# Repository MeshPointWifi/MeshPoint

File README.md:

# MeshPoint
MeshPoint is Open source Wifi Hotspot for Crisis Situations
www.meshpointone.com

## MeshPoint v4.1

## Technical Specifications

- **CPU / SoC:** 700 MHz Quad-core Cortex-A7 / Qualcomm IPQ4018
- **RAM memory and storage:** 128 MB NAND and 8 MB NOR flash, 256 MB DDR3 RAM
- **Wi-Fi standards:** 802.11 a/b/g/n/ac Wave 2
- **Mesh protocol:** 802.11s mesh networking protocol
- **Radio:** 2.4 GHz and 5 GHz dual band
- **MIMO:** 2.4 GHz 2x2 MIMO / 5.8 GHz 2x2 MIMO
- **VLAN:** 802.1Q VLAN
- **Monitoring:** SNMP v2 / SNMP v3
- **Environment:** Indoor / Outdoor
- **Concurrent clients:** 300+
- **PoE mode:** Passive PoE in and PoE out
- **Power supply:** Battery powered, solar powered or PoE in
- **Antennas:** Internal dual-band antennas, 7 dBi
- **Wireless security:** WEP, WPA-PSK, WPA-Enterprise (WPA/WPA2, TKIP/AES), WPA3
- **Power consumption:** Average 4 W, maximum 12 W
- **Maximum TX power:** 20 dBm
- **Operating temperature:** -40 °C to 70 °C (-40 °F to 158 °F)
- **Licence:** Free
- **Available interfaces:** USB 2.0, USB 3.0, I2C, I2S, TDM, SPI, UART, GPIO, JTAG
- **Network ports:** 2x 1000BASE-T Ethernet ports
- **LTE modem option:** USB LTE Cat 4 modem

## New features

- [x] PoE Passtrough ( IN + OUT - daisy-chain )
- [x] On board sensor PRESSURE HUMIDITY TEMP
- [x] PCF8563T - on board RTC

## Licence

This project (hardware designs, 3D files and documentation) is released under the
**CERN Open Hardware Licence Version 2 - Strongly Reciprocal (CERN-OHL-S v2)**.

See the [LICENCE](LICENCE) file for the full text.
More info: https://cern-ohl.web.cern.ch/

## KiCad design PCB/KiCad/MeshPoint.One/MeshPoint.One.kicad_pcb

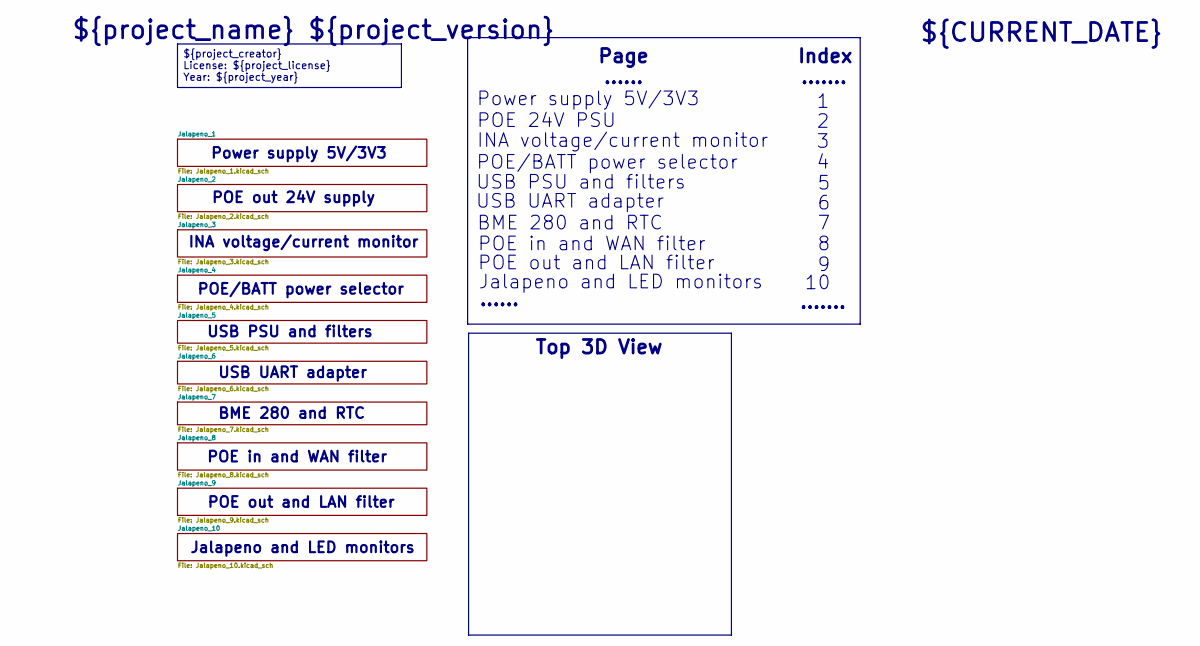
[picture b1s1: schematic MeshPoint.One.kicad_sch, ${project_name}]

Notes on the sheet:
POE/BATT power selector
${project_name} ${project_version}
Power supply 5V/3V3
Index
POE in and WAN filter
USB UART adapter
POE 24V PSU
POE out 24V supply
POE out and LAN filter
Jalapeno and LED monitors
BME 280 and RTC
INA voltage/current monitor
.......
USB PSU and filters
......
Page
Top 3D View
${CURRENT_DATE}
${project_creator} License: ${project_license} Year: ${project_year}

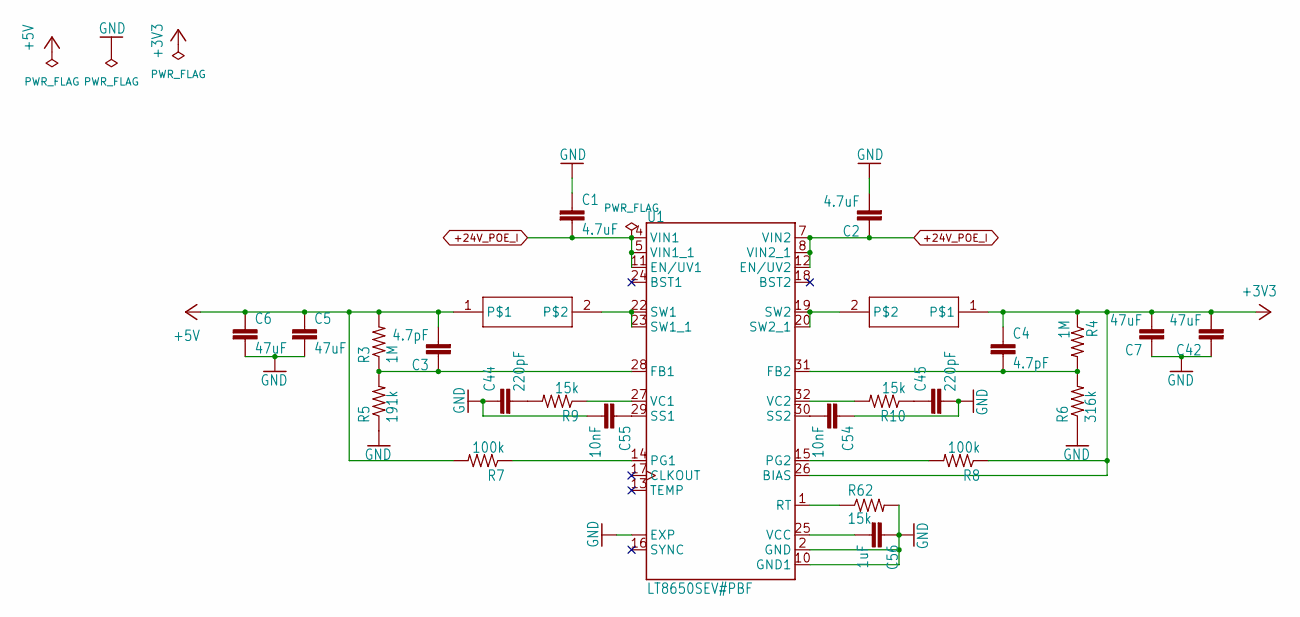
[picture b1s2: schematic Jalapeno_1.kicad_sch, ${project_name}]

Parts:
C1, C2: 4.7uF; C_1206_3216Metric; LCSC C29823
C3, C4: 4.7pF; C_0402_1005Metric; LCSC C1569
C5, C6, C7, C42: 47uF; C_1206_3216Metric; LCSC C96123
C44, C45: 220pF; C_0402_1005Metric; LCSC C1530
C54, C55: 10nF; C_0402_1005Metric; LCSC C1524
C56: 1uF; C_0402_1005Metric; LCSC C307413
L1, L2: PA4333.102NLTPA4333.102NLT; INDC6932X320; LCSC C5151941
R3, R4: 1M; R_0402_1005Metric; LCSC C279988
R5: 191k; R_0402_1005Metric; LCSC C852583
R6: 316k; R_0402_1005Metric; LCSC C25777
R7, R8: 100k; R_0402_1005Metric; LCSC C25741
R9, R10, R62: 15k; R_0402_1005Metric; LCSC C25756
U1: LT8650SEV#PBF; QFN50P600X400X103-32N240X440; Mouser 584-LT8650SEV#PBF

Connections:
+3V3: C4.1, C7.2, C42.2, L2.1, R4.1, R8.1, U1.26 (BIAS); also elsewhere on the board
+5V: C3.2, C5.1, C6.1, L1.1, R3.2, R7.2; also elsewhere on the board
+24V_POE_I: C1.2, C2.1, U1.4 (VIN1), U1.5 (VIN1_1), U1.7 (VIN2), U1.8 (VIN2_1), U1.11 (EN/UV1), U1.12 (EN/UV2); also elsewhere on the board
GND: C1.1, C2.2, C5.2, C6.2, C7.1, C42.1, C44.1, C45.2, C54.1, C55.2, C56.1, R5.1, R6.1, R62.2, U1.2 (GND), U1.10 (GND1), U1.33 (EXP), U1.34 (EXP), U1.35 (EXP), U1.36 (EXP), U1.37 (EXP), U1.38 (EXP); also elsewhere on the board
unnamed: C44.2, R9.2
unnamed: C45.1, R10.1
unnamed: L1.2, U1.22 (SW1), U1.23 (SW1_1)
unnamed: L2.2, U1.19 (SW2), U1.20 (SW2_1)
unnamed: C3.1, R3.1, R5.2, U1.28 (FB1)
unnamed: C4.2, R4.2, R6.2, U1.31 (FB2)
unnamed: R7.1, U1.14 (PG1)
unnamed: R8.2, U1.15 (PG2)
unnamed: R62.1, U1.1 (RT)
unnamed: C55.1, U1.29 (SS1)
unnamed: C54.2, U1.30 (SS2)
unnamed: R9.1, U1.27 (VC1)
unnamed: R10.2, U1.32 (VC2)
unnamed: C56.2, U1.25 (VCC)

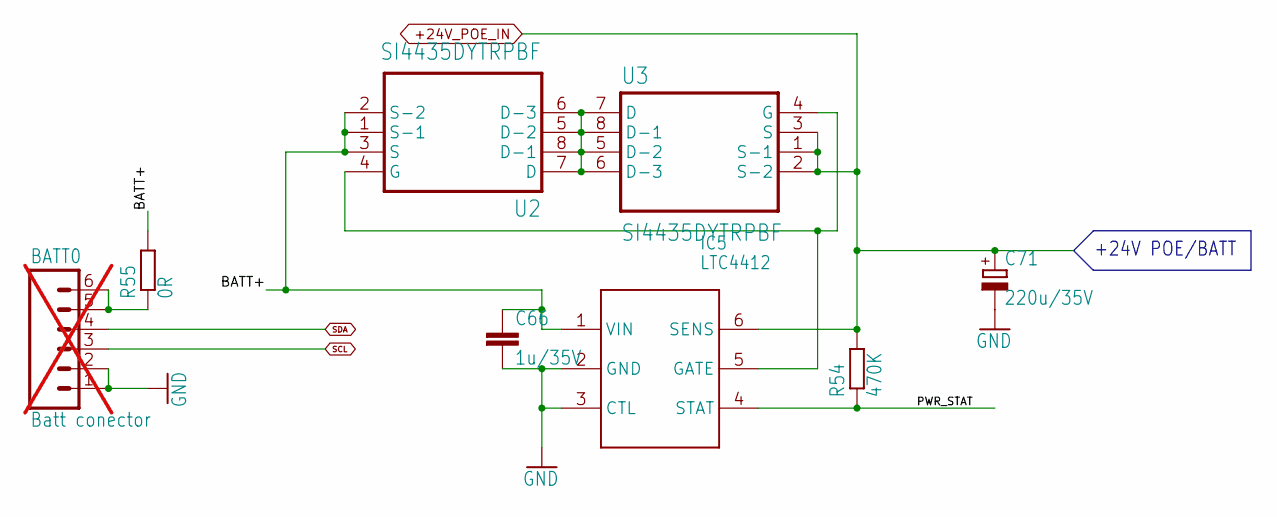
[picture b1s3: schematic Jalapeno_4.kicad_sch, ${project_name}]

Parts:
BATT0: Batt conector; 06P; LCSC C87216; not fitted
C66: 1u/35V; C_0402_1005Metric; LCSC C307413
C71: 220u/35V; 153CLV-1010; LCSC C178562
IC5: LTC4412; TSOT-23-6; LCSC C514442
R54: 470K; R_0402_1005Metric; LCSC C25799
R55: 0R; R_0805_2012Metric; LCSC C17477
U2, U3: SI4435DYTRPBF; SOIC-8_3.9x4.9mm_P1.27mm; LCSC C67287

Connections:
+24V_POE_IN: C71.+, IC5.6 (SENS), R54.2, U3.1 (S-1), U3.2 (S-2), U3.3 (S); also elsewhere on the board
/Jalapeno_4/BATT+: C66.1, IC5.1 (VIN), R55.2, U2.1 (S-1), U2.2 (S-2), U2.3 (S)
/Jalapeno_4/PWR_STAT: IC5.4 (STAT), R54.1
GND: BATT0.1, BATT0.2, C66.2, C71.-, IC5.2 (GND), IC5.3 (CTL); also elsewhere on the board
unnamed: BATT0.5, BATT0.6, R55.1
unnamed: IC5.5 (GATE), U2.4 (G), U3.4 (G)
unnamed: U2.5 (D-2), U2.6 (D-3), U2.7 (D), U2.8 (D-1), U3.5 (D-2), U3.6 (D-3), U3.7 (D), U3.8 (D-1)
SCL: BATT0.3; also elsewhere on the board
SDA: BATT0.4; also elsewhere on the board

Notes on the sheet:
+24V POE/BATT

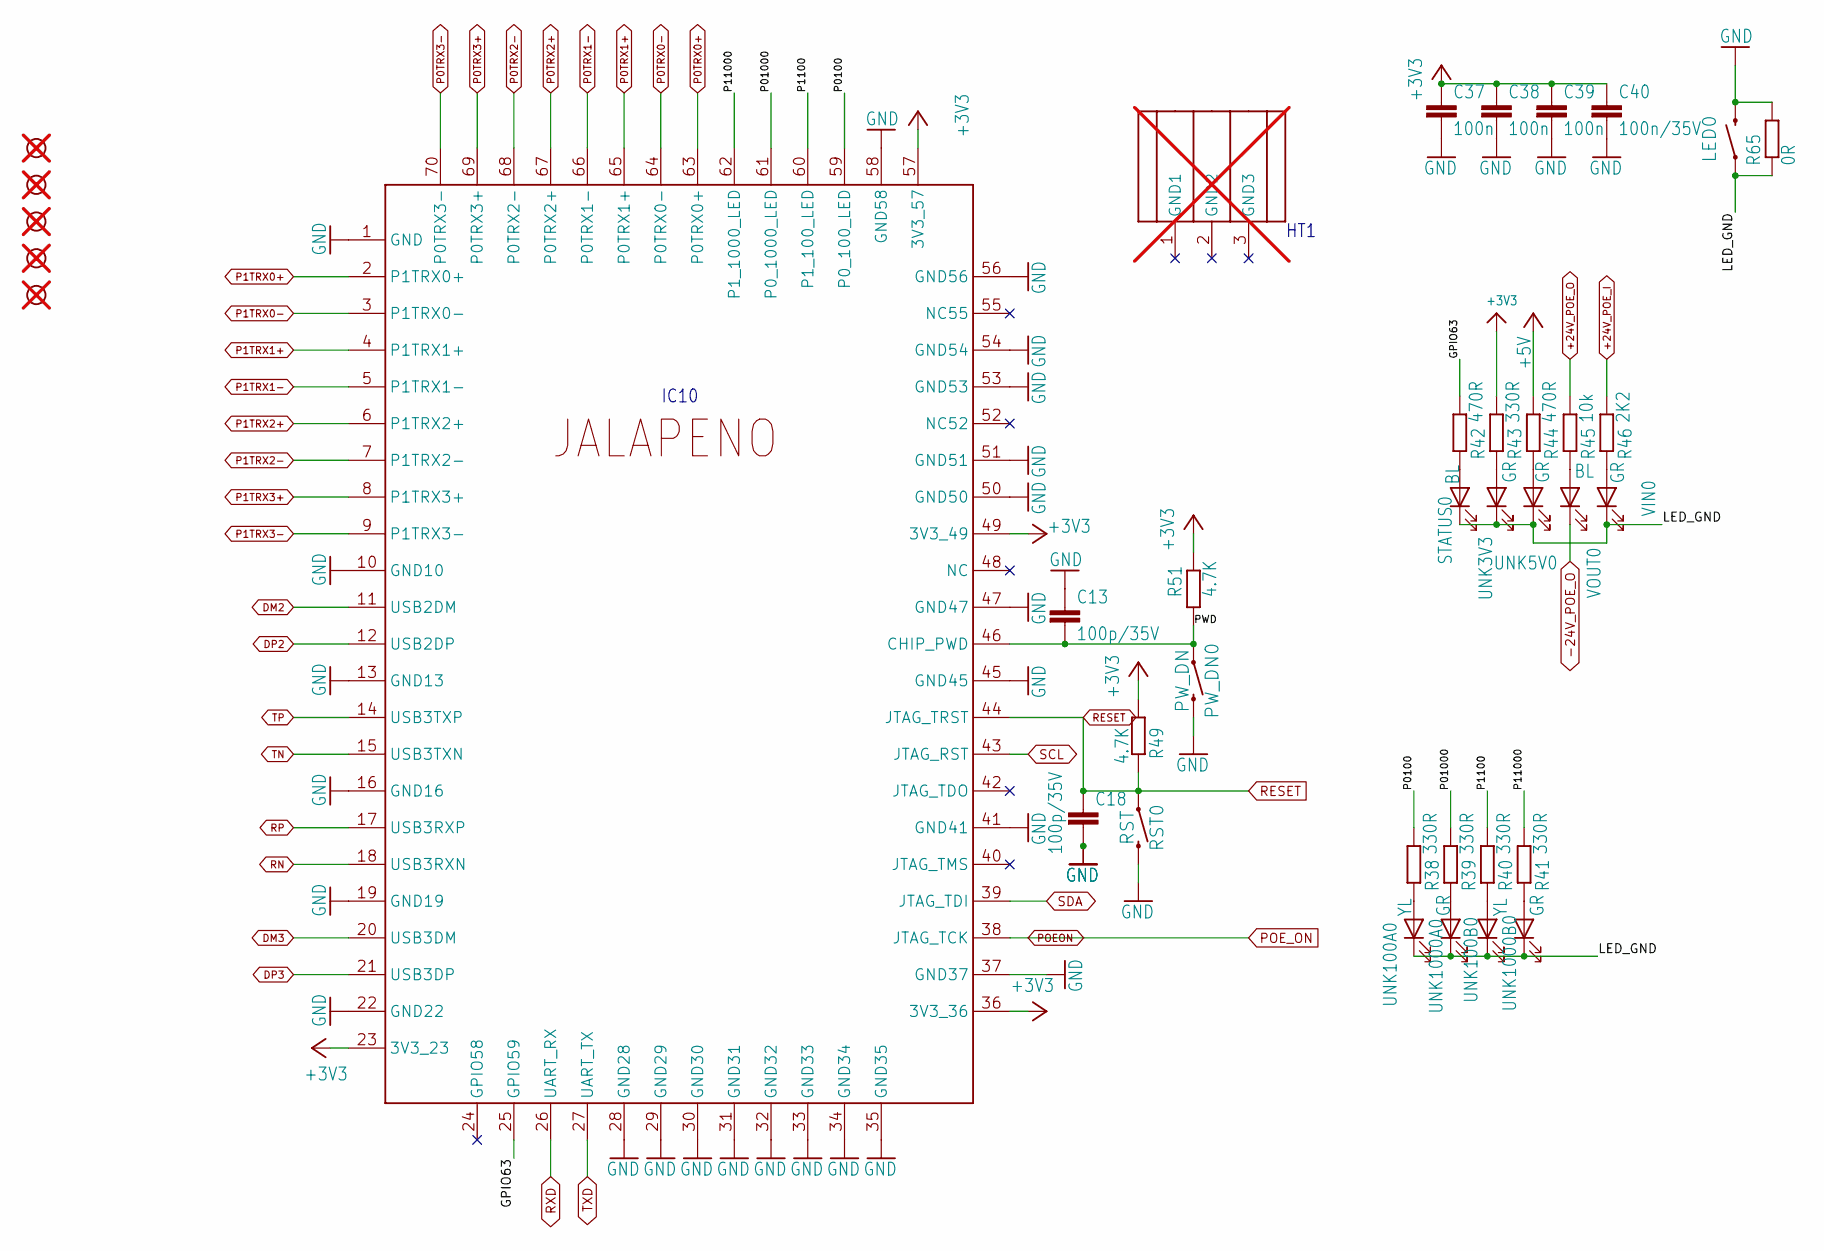
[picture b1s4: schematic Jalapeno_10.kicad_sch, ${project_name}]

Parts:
C13, C18: 100p/35V; C_0402_1005Metric; LCSC C1546
C37, C38, C39: 100n; C_0402_1005Metric; LCSC C187828
C40: 100n/35V; C_0402_1005Metric; LCSC C187828
FD1, FD2, FD3, FD4, FD5: FIDUCIALUFIDUCIAL; FIDUCIAL-MICRO_507; not fitted
LED0: MOMENTARY-SWITCH-SPST-SMD-4.6X2.8MM; TACTILE_SWITCH_SMD_4.6X2.8MM_535; LCSC C72443
PW_DN0: PW_DN; TACTILE_SWITCH_SMD_4.6X2.8MM_535; LCSC C72443
R38, R39, R40, R41, R43: 330R; R_0402_1005Metric; LCSC C25104
R42, R44: 470R; R_0402_1005Metric; LCSC C25117
R45: 10k; R_0402_1005Metric; LCSC C25744
R46: 2K2; R_0402_1005Metric; LCSC C25879
R49, R51: 4.7K; R_0402_1005Metric; LCSC C25900
R65: 0R; R_0805_2012Metric; LCSC C17477
RST0: RST; TACTILE_SWITCH_SMD_4.6X2.8MM_535; LCSC C72443
STATUS0: BL; LED_0603_1608Metric; LCSC C2288
U$5: JALAPENO; JALAPENO-PCB
U$9: HEATSINK; not fitted
UNK3V3, UNK5V0, UNK1000A0, UNK1000B0: GR; LED_0603_1608Metric; LCSC C72043
UNK100A0, UNK100B0: YL; LED_0603_1608Metric; LCSC C72038
VIN0: GR; LED_0603_1608Metric; LCSC C72043
VOUT0: BL; LED_0603_1608Metric; LCSC C2288

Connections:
+3V3: C37.1, C38.1, C39.1, C40.1, R43.2, R49.1, R51.2, U$5.23 (3V3_23), U$5.36 (3V3_36), U$5.49 (3V3_49), U$5.57 (3V3_57); also elsewhere on the board
+5V: R44.2; also elsewhere on the board
+24V_POE_I: R46.2; also elsewhere on the board
+24V_POE_O: R45.2; also elsewhere on the board
-24V_POE_O: VOUT0.1 (K); also elsewhere on the board
/Jalapeno_10/GPIO63: R42.2, U$5.25 (GPIO59)
/Jalapeno_10/LED_GND: LED0.1, LED0.2 (1), R65.1, STATUS0.1 (K), UNK3V3.1 (K), UNK5V0.1 (K), UNK100A0.1 (K), UNK100B0.1 (K), UNK1000A0.1 (K), UNK1000B0.1 (K), VIN0.1 (K)
/Jalapeno_10/P0100: R38.2, U$5.59 (P0_100_LED)
/Jalapeno_10/P01000: R39.2, U$5.61 (P0_1000_LED)
/Jalapeno_10/P1100: R40.2, U$5.60 (P1_100_LED)
/Jalapeno_10/P11000: R41.2, U$5.62 (P1_1000_LED)
/Jalapeno_10/PWD: C13.2, PW_DN0.1, PW_DN0.2 (1), R51.1, U$5.46 (CHIP_PWD)
DM2: U$5.11 (USB2DM); also elsewhere on the board
DM3: U$5.20 (USB3DM); also elsewhere on the board
DP2: U$5.12 (USB2DP); also elsewhere on the board
DP3: U$5.21 (USB3DP); also elsewhere on the board
GND: C13.1, C18.2, C37.2, C38.2, C39.2, C40.2, LED0.3 (2), LED0.4 (2), PW_DN0.3 (2), PW_DN0.4 (2), R65.2, RST0.3 (2), RST0.4 (2), U$5.1 (GND), U$5.10 (GND10), U$5.13 (GND13), U$5.16 (GND16), U$5.19 (GND19), U$5.22 (GND22), U$5.28 (GND28), U$5.29 (GND29), U$5.30 (GND30), U$5.31 (GND31), U$5.32 (GND32), U$5.33 (GND33), U$5.34 (GND34), U$5.35 (GND35), U$5.37 (GND37), U$5.41 (GND41), U$5.45 (GND45), U$5.47 (GND47), U$5.50 (GND50), U$5.51 (GND51), U$5.53 (GND53), U$5.54 (GND54), U$5.56 (GND56), U$5.58 (GND58); also elsewhere on the board
unnamed: R42.1, STATUS0.2 (A)
unnamed: R43.1, UNK3V3.2 (A)
unnamed: R44.1, UNK5V0.2 (A)
unnamed: R38.1, UNK100A0.2 (A)
unnamed: R40.1, UNK100B0.2 (A)
unnamed: R39.1, UNK1000A0.2 (A)
unnamed: R41.1, UNK1000B0.2 (A)
unnamed: R46.1, VIN0.2 (A)
unnamed: R45.1, VOUT0.2 (A)
P0TRX0+: U$5.63 (P0TRX0+); also elsewhere on the board
P0TRX0-: U$5.64 (P0TRX0-); also elsewhere on the board
P0TRX1+: U$5.65 (P0TRX1+); also elsewhere on the board
P0TRX1-: U$5.66 (P0TRX1-); also elsewhere on the board
P0TRX2+: U$5.67 (P0TRX2+); also elsewhere on the board
P0TRX2-: U$5.68 (P0TRX2-); also elsewhere on the board
P0TRX3+: U$5.69 (P0TRX3+); also elsewhere on the board
P0TRX3-: U$5.70 (P0TRX3-); also elsewhere on the board
P1TRX0+: U$5.2 (P1TRX0+); also elsewhere on the board
P1TRX0-: U$5.3 (P1TRX0-); also elsewhere on the board
P1TRX1+: U$5.4 (P1TRX1+); also elsewhere on the board
P1TRX1-: U$5.5 (P1TRX1-); also elsewhere on the board
P1TRX2+: U$5.6 (P1TRX2+); also elsewhere on the board
P1TRX2-: U$5.7 (P1TRX2-); also elsewhere on the board
P1TRX3+: U$5.8 (P1TRX3+); also elsewhere on the board
P1TRX3-: U$5.9 (P1TRX3-); also elsewhere on the board
POE out ON: U$5.38 (JTAG_TCK); also elsewhere on the board
RESET: C18.1, R49.2, RST0.1, RST0.2 (1), U$5.44 (JTAG_TRST); also elsewhere on the board
RN: U$5.18 (USB3RXN); also elsewhere on the board
RP: U$5.17 (USB3RXP); also elsewhere on the board
RXD: U$5.26 (UART_RX); also elsewhere on the board
SCL: U$5.43 (JTAG_RST); also elsewhere on the board
SDA: U$5.39 (JTAG_TDI); also elsewhere on the board
TN: U$5.15 (USB3TXN); also elsewhere on the board
TP: U$5.14 (USB3TXP); also elsewhere on the board
TXD: U$5.27 (UART_TX); also elsewhere on the board

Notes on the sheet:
HT1
IC10

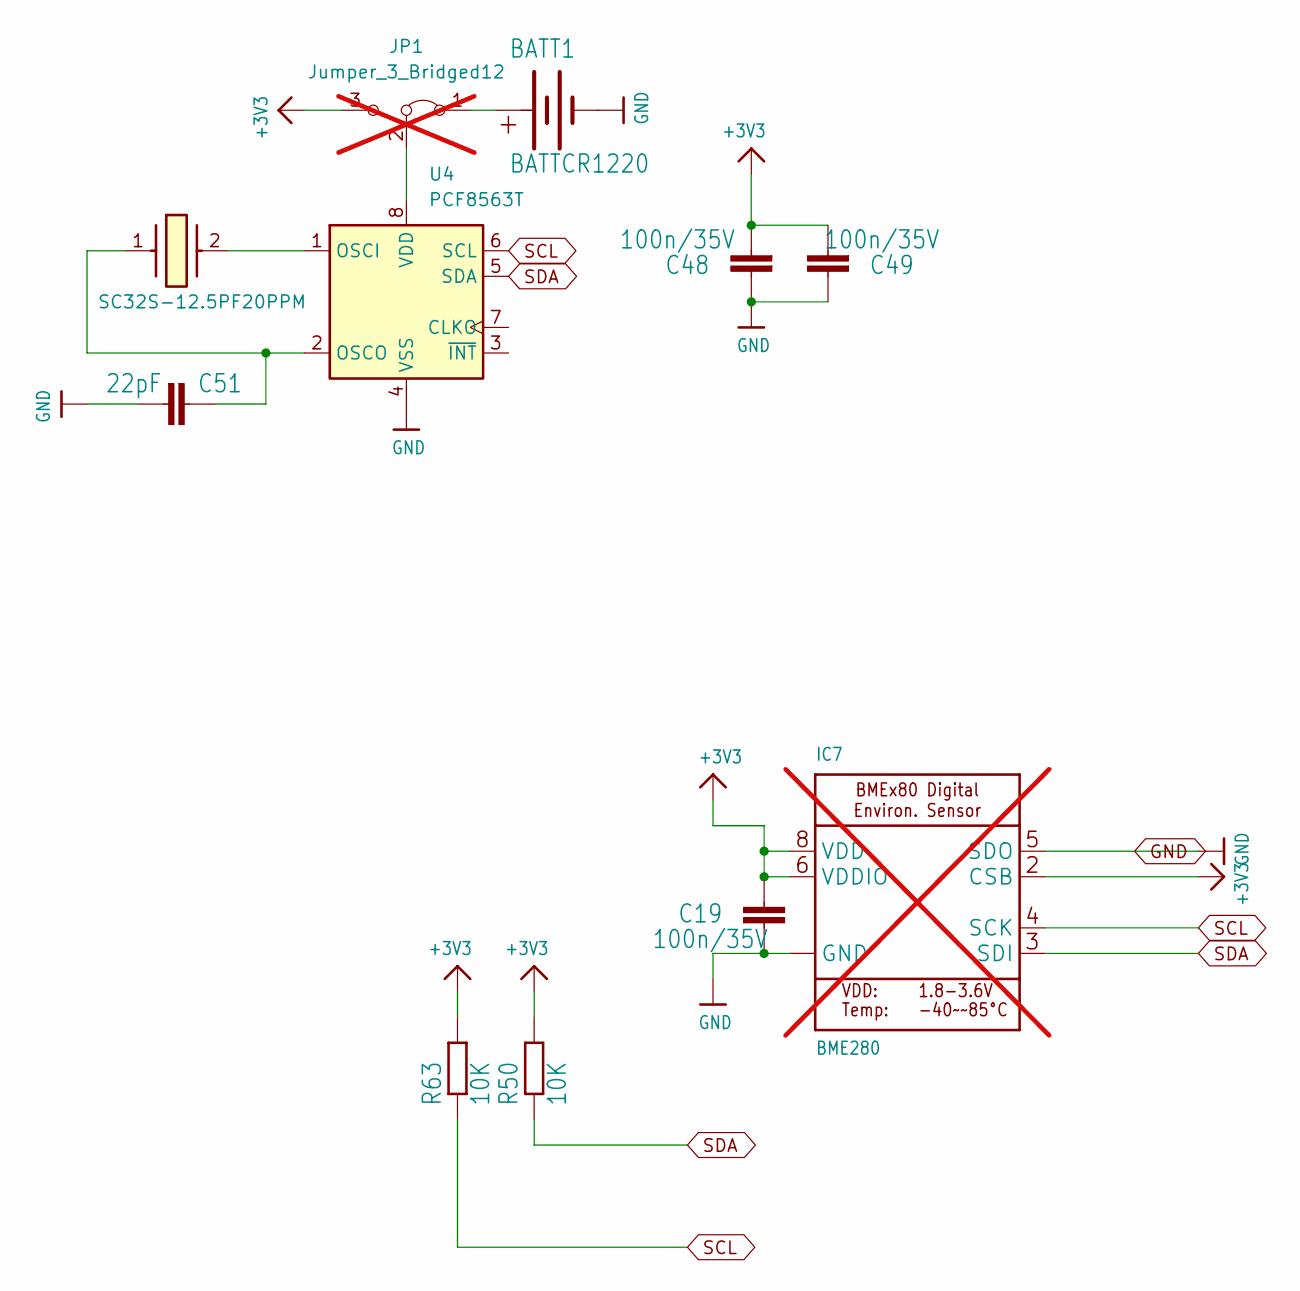
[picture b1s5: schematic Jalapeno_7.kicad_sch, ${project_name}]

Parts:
BATT1: BATTCR1220; BATERIJA12MM; LCSC C70377
C19, C48, C49: 100n/35V; C_0402_1005Metric; LCSC C187828
C51: 22pF; C_0402_1005Metric; LCSC C1555
IC7: BME280; Bosch_LGA-8_2.5x2.5mm_P0.65mm_ClockwisePinNumbering; LCSC C92489; not fitted
JP1: Jumper_3_Bridged12; SolderJumper-3_P1.3mm_Open_RoundedPad1.0x1.5mm_NumberLabels; not fitted
R50, R63: 10K; R_0402_1005Metric; LCSC C25744
U4: PCF8563T; SOIC-8_3.9x4.9mm_P1.27mm; LCSC C7440
Y1: SC32S-12.5PF20PPM; SC32S125PF20PPM; Mouser Part Number 628-SC32S-125PF20PPM

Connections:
+3V3: C19.1, C48.2, C49.2, IC7.2 (CSB), IC7.6 (VDDIO), IC7.8 (VDD), JP1.3 (B), R50.2, R63.2; also elsewhere on the board
GND: BATT1.-, C19.2, C48.1, C49.1, C51.2, IC7.1 (GND), IC7.5 (SDO), IC7.7 (GND), U4.4 (VSS); also elsewhere on the board
unnamed: BATT1.+, JP1.1 (A)
unnamed: JP1.2 (C), U4.8 (VDD)
unnamed: U4.1 (OSCI), Y1.2
unnamed: C51.1, U4.2 (OSCO), Y1.1
SCL: IC7.4 (SCK), R63.1, U4.6 (SCL); also elsewhere on the board
SDA: IC7.3 (SDI), R50.1, U4.5 (SDA); also elsewhere on the board

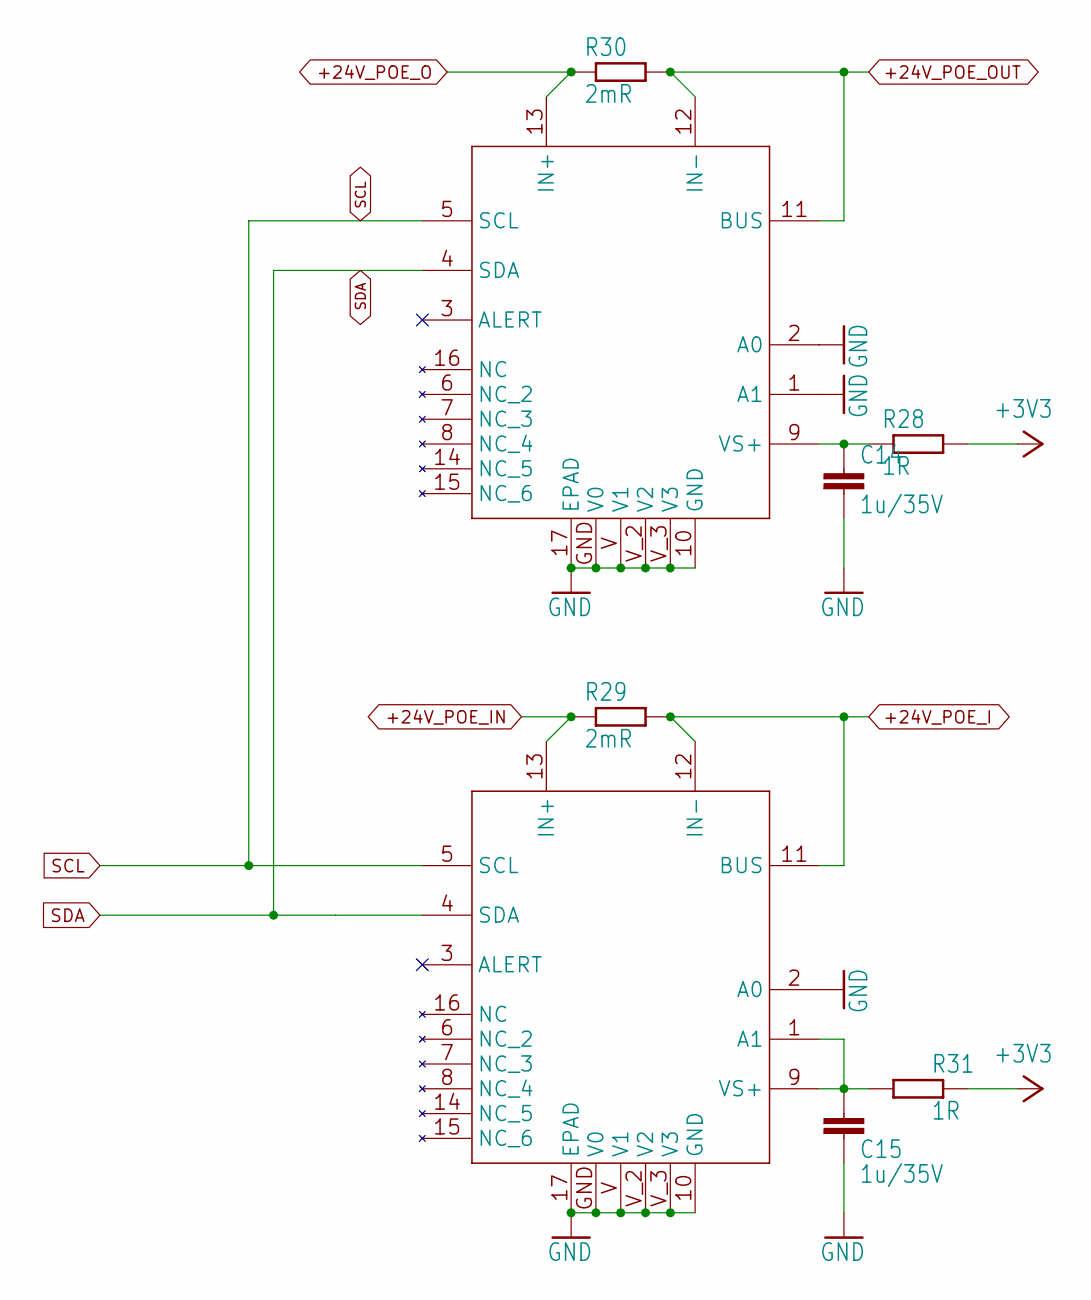
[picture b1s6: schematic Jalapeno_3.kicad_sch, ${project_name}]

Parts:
C14, C15: 1u/35V; C_0402_1005Metric; LCSC C307413
IC3, IC4: INA230_RGT_16; QFN-16-1EP_3x3mm_P0.5mm_EP1.7x1.7mm; LCSC C882784
R28, R31: 1R; R_0402_1005Metric; LCSC C25086
R29, R30: 2mR; R_2010_5025Metric; LCSC C844078

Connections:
+3V3: R28.2, R31.2; also elsewhere on the board
+24V_POE_I: IC4.11 (BUS), IC4.12 (IN-), R29.2; also elsewhere on the board
+24V_POE_IN: IC4.13 (IN+), R29.1; also elsewhere on the board
+24V_POE_O: IC3.13 (IN+), R30.1; also elsewhere on the board
+24V_POE_OUT: IC3.11 (BUS), IC3.12 (IN-), R30.2; also elsewhere on the board
GND: C14.2, C15.2, IC3.1 (A1), IC3.2 (A0), IC3.10 (GND), IC3.17 (EPAD), IC3.GND (V0), IC3.V (V1), IC3.V_2 (V2), IC3.V_3 (V3), IC4.2 (A0), IC4.10 (GND), IC4.17 (EPAD), IC4.GND (V0), IC4.V (V1), IC4.V_2 (V2), IC4.V_3 (V3); also elsewhere on the board
unnamed: C14.1, IC3.9 (VS+), R28.1
unnamed: C15.1, IC4.1 (A1), IC4.9 (VS+), R31.1
SCL: IC3.5 (SCL), IC4.5 (SCL); also elsewhere on the board
SDA: IC3.4 (SDA), IC4.4 (SDA); also elsewhere on the board

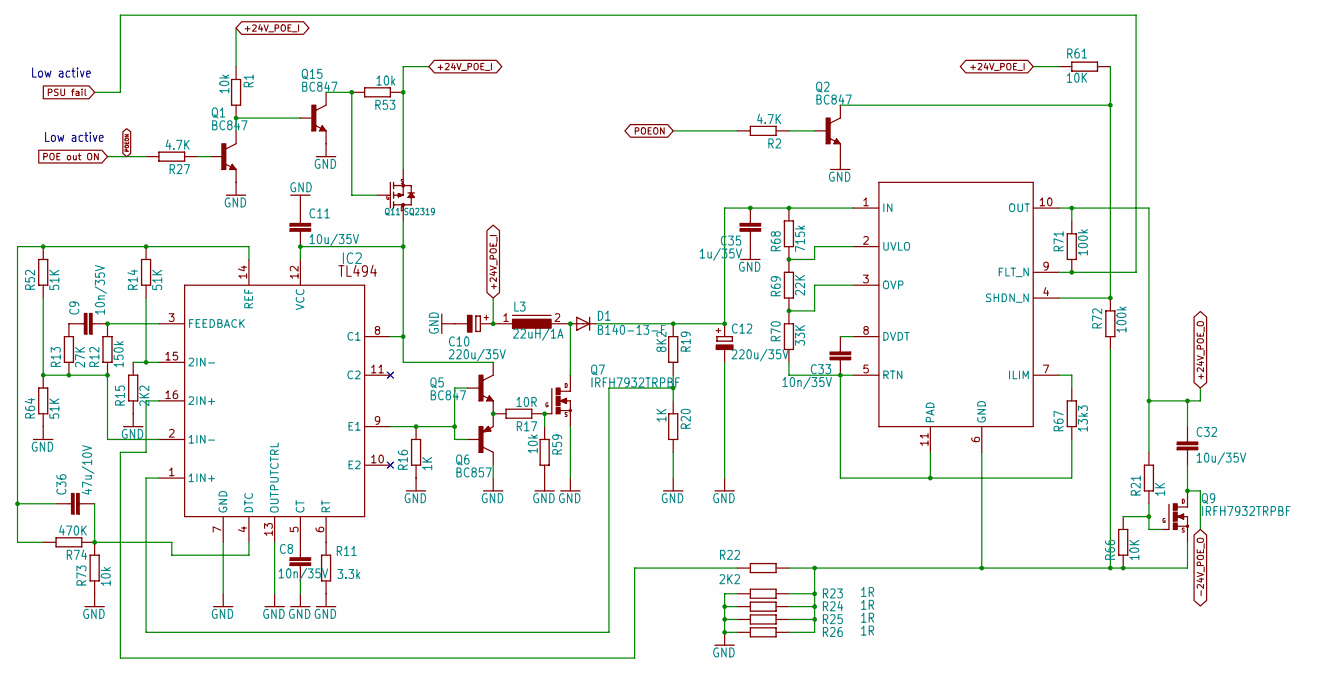
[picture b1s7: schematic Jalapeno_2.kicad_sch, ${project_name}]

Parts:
C8, C9, C33: 10n/35V; C_0402_1005Metric; LCSC C1524
C10, C12: 220u/35V; 153CLV-1010; LCSC C178562
C11, C32: 10u/35V; C_1206_3216Metric; LCSC C13585
C35: 1u/35V; C_0402_1005Metric; LCSC C307413
C36: 47u/10V; C_1206_3216Metric; LCSC C5448950
D1: B140-13-F; SMB; LCSC C134426
IC2: TL494CPWR; TSSOP-16_4.4x5mm_P0.65mm; LCSC C22396897
IC11: TPS26623DRCR; Texas_DRC0010J; LCSC C2155839
L3: 22uH/1A; L_12x12mm_H6mm; LCSC C2879697
Q1, Q2, Q5, Q15: BC847; SOT-23; LCSC C8664
Q6: BC857; SOT23-BEC; LCSC C8549
Q7, Q9: IRFH7932TRPBF; PG-TDSON-8; Mouser 942-IRFH7932TRPBF
Q11: SQ2319; SOT-23; LCSC C3280190
R1, R53, R59, R73: 10k; R_0402_1005Metric; LCSC C25744
R2, R27: 4.7K; R_0402_1005Metric; LCSC C25900
R11: 3.3k; R_0402_1005Metric; LCSC C25890
R12: 150k; R_0402_1005Metric; LCSC C25755
R13: 27K; R_0402_1005Metric; LCSC C25771
R14, R52, R64: 51K; R_0402_1005Metric; LCSC C25794
R15, R22: 2K2; R_0402_1005Metric; LCSC C25879
R16, R20, R21: 1K; R_0402_1005Metric; LCSC C11702
R17: 10R; R_0402_1005Metric; LCSC C25077
R19: 8K2; R_0402_1005Metric; LCSC C137929
R23, R24, R25, R26: 1R; R_1206_3216Metric; LCSC C17928
R61, R66: 10K; R_0402_1005Metric; LCSC C25744
R67: 13k3; R_0402_1005Metric; LCSC C3015832
R68: 715k; R_0402_1005Metric; LCSC C5126240
R69: 22K; R_0402_1005Metric; LCSC C25768
R70: 33K; R_0402_1005Metric; LCSC C25779
R71, R72: 100k; R_0402_1005Metric; LCSC C25741
R74: 470K; R_0402_1005Metric; LCSC C25799

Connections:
+24V_POE_I: C10.+, L3.1, Q11.2 (S), R1.1, R53.1, R61.1; also elsewhere on the board
+24V_POE_O: C32.1, IC11.10 (OUT), R21.2, R71.2; also elsewhere on the board
-24V_POE_O: C32.2, Q9.5 (D), Q9.6 (D), Q9.7 (D), Q9.8 (D), Q9.TH (D); also elsewhere on the board
GND: C8.2, C10.-, C11.1, C12.-, C35.1, IC2.7 (GND), IC2.13 (OUTPUTCTRL), Q1.2 (E), Q2.2 (E), Q6.C, Q7.1 (S), Q7.2 (S), Q7.3 (S), Q15.2 (E), R11.1, R15.1, R16.1, R20.2, R23.1, R24.1, R25.1, R26.1, R59.2, R64.1, R73.1; also elsewhere on the board
unnamed: C9.1, R13.2
unnamed: D1.A, L3.2, Q7.5 (D), Q7.6 (D), Q7.7 (D), Q7.8 (D), Q7.TH (D)
unnamed: IC2.1 (1IN+), R19.2, R20.1
unnamed: IC2.2 (1IN-), R12.1, R13.1, R52.1, R64.2
unnamed: IC2.16 (2IN+), R22.1
unnamed: IC2.15 (2IN-), R14.1, R15.2
unnamed: C11.2, IC2.8 (C1), IC2.12 (VCC), Q5.3 (C), Q11.3 (D)
unnamed: C8.1, IC2.5 (CT)
unnamed: C36.2, IC2.4 (DTC), R73.2, R74.1
unnamed: IC2.9 (E1), Q5.1 (B), Q6.B, R16.2
unnamed: C9.2, IC2.3 (FEEDBACK), R12.2
unnamed: C36.1, IC2.14 (REF), R14.2, R52.2, R74.2
unnamed: IC2.6 (RT), R11.2
unnamed: C33.2, IC11.8 (DVDT)
unnamed: IC11.6 (GND), Q9.1 (S), Q9.2 (S), Q9.3 (S), R22.2, R23.2, R24.2, R25.2, R26.2, R66.1, R72.1
unnamed: IC11.7 (ILIM), R67.2
unnamed: C12.+, C35.2, D1.C, IC11.1 (IN), R19.1, R68.2
unnamed: IC11.3 (OVP), R69.1, R70.2
unnamed: C33.1, IC11.5 (RTN), IC11.11 (PAD), R67.1, R70.1
unnamed: IC11.4 (SHDN_N), Q2.3 (C), R61.2, R72.2
unnamed: IC11.2 (UVLO), R68.1, R69.2
unnamed: Q1.1 (B), R27.1
unnamed: Q1.3 (C), Q15.1 (B), R1.2
unnamed: Q2.1 (B), R2.1
unnamed: Q5.2 (E), Q6.E, R17.2
unnamed: Q7.4 (G), R17.1, R59.1
unnamed: Q9.4 (G), R21.1, R66.2
unnamed: Q11.1 (G), Q15.3 (C), R53.2
POE out ON: R2.2, R27.2; also elsewhere on the board
PSU fail: IC11.9 (FLT_N), R71.1

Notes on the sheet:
Low active

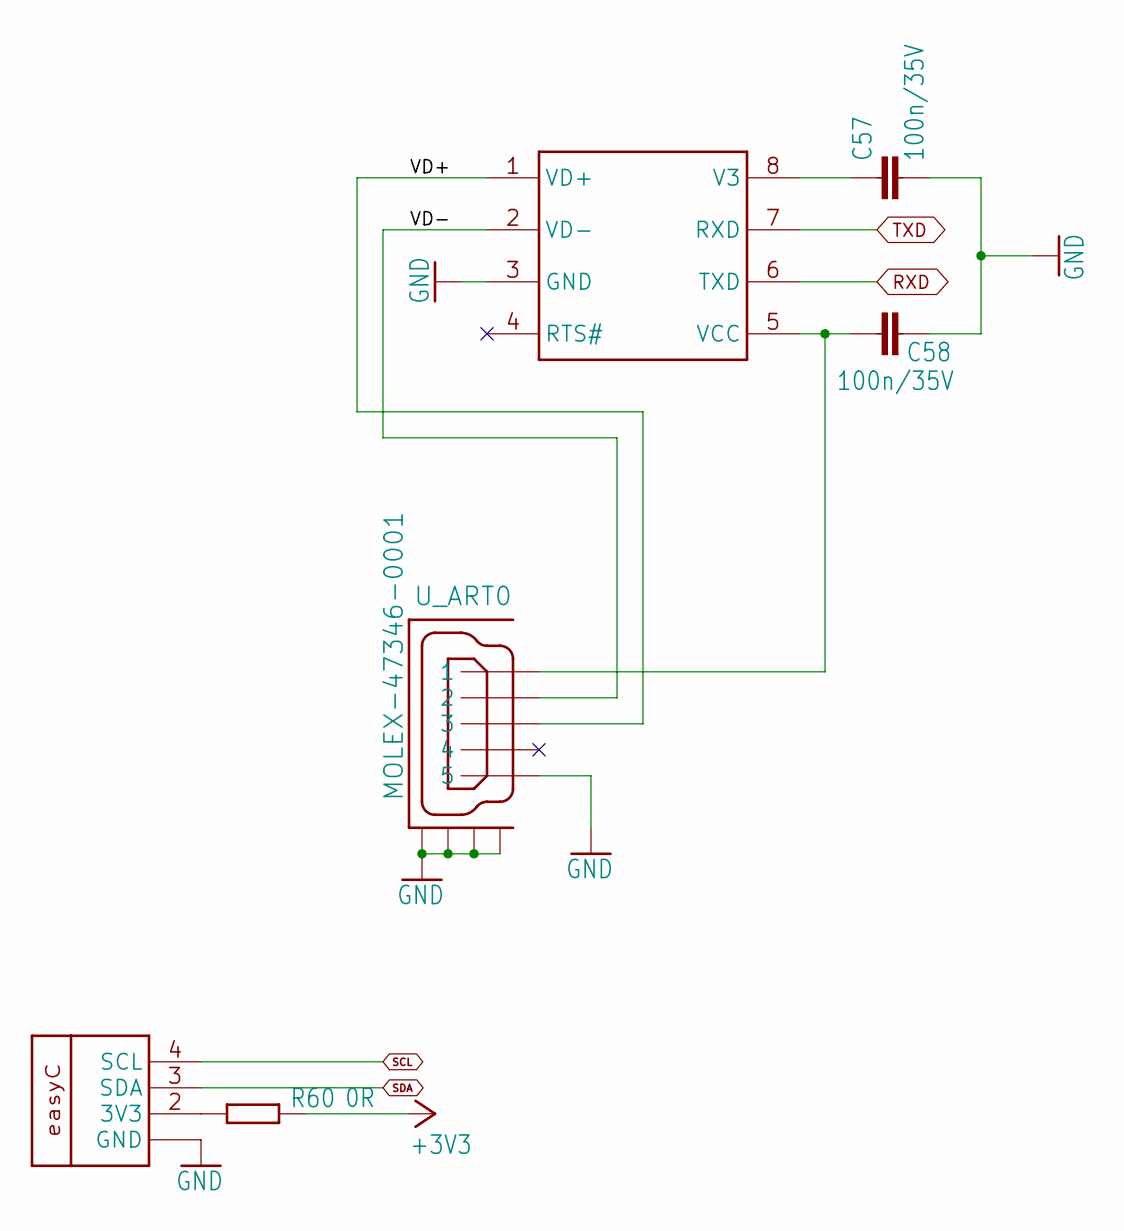
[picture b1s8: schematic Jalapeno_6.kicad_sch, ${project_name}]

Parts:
C57, C58: 100n/35V; C_0402_1005Metric; LCSC C187828
CN2: EASYC; LCSC C160404
IC10: CH340N; SOIC-8_3.9x4.9mm_P1.27mm; LCSC C2977777
R60: 0R; R_0805_2012Metric; LCSC C17477
U_ART0: MOLEX-47346-0001; MOLEX-47364-0001; LCSC C232975

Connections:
+3V3: R60.2; also elsewhere on the board
/Jalapeno_6/VD+: IC10.1 (VD+), U_ART0.3
/Jalapeno_6/VD-: IC10.2 (VD-), U_ART0.2
GND: C57.2, C58.2, CN2.1 (GND), CN2.NC1 (GND), CN2.NC2 (GND), IC10.3 (GND), U_ART0.5, U_ART0.GND1, U_ART0.GND2, U_ART0.GND3, U_ART0.GND4; also elsewhere on the board
unnamed: CN2.2 (3V3), R60.1
unnamed: C57.1, IC10.8 (V3)
unnamed: C58.1, IC10.5 (VCC), U_ART0.1
RXD: IC10.6 (TXD); also elsewhere on the board
SCL: CN2.4 (SCL); also elsewhere on the board
SDA: CN2.3 (SDA); also elsewhere on the board
TXD: IC10.7 (RXD); also elsewhere on the board

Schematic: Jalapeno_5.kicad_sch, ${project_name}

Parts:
C16, C20, C46: 100n/35V; C_0402_1005Metric; LCSC C187828
C17, C47: 10u/35V; C_1206_3216Metric; LCSC C13585
IC6: TPS2052B_DGN; DGN8_1P89X1P57; LCSC C2879167
L4, L5, L6, L7, L8, L9, L10, L11: 1nH; R_0402_1005Metric; LCSC C19633897
R32, R33: 10K; R_0402_1005Metric; LCSC C25744
R34, R35: 3.3K; R_0402_1005Metric; LCSC C25890
USB3.0: USB3.0D; Mouser 530-SS-52000-003

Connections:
+5V: C20.2, IC6.2 (IN), R32.1, R33.1, R34.1, R35.1; also elsewhere on the board
DM2: L11.1; also elsewhere on the board
DM3: L9.2; also elsewhere on the board
DP2: L10.1; also elsewhere on the board
DP3: L8.2; also elsewhere on the board
GND: C16.2, C17.1, C20.1, C46.1, C47.2, IC6.1 (GND), IC6.EPAD, USB3.0.4 (GND), USB3.0.7 (GND_DR), USB3.0.13 (1GND), USB3.0.16 (1GND_DR), USB3.0.PAD1, USB3.0.PAD2, USB3.0.PAD3, USB3.0.PAD4; also elsewhere on the board
unnamed: C17.2, C46.2, IC6.7 (OUT), USB3.0.1 (VBUS)
unnamed: C16.1, C47.1, IC6.6 (OUT_2), USB3.0.10 (1VBUS)
unnamed: IC6.3 (~EN1), R32.2
unnamed: IC6.4 (~EN2), R33.2
unnamed: IC6.8 (~OC1), R34.2
unnamed: IC6.5 (~OC2), R35.2
unnamed: L8.1, USB3.0.12 (1D+)
unnamed: L9.1, USB3.0.11 (1D-)
unnamed: L6.1, USB3.0.15 (1SSRX+)
unnamed: L7.1, USB3.0.14 (1SSRX-)
unnamed: L4.1, USB3.0.18 (1SSTX+)
unnamed: L5.1, USB3.0.17 (1SSTX-)
unnamed: L10.2, USB3.0.3 (D+)
unnamed: L11.2, USB3.0.2 (D-)
RN: L7.2; also elsewhere on the board
RP: L6.2; also elsewhere on the board
TN: L5.2; also elsewhere on the board
TP: L4.2; also elsewhere on the board

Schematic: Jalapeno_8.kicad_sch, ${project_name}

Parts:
B1, B2: 1A/50V; MBS; LCSC C2488
C21, C23, C24, C25: 100n/35V; C_0402_1005Metric; LCSC C187828
C22: 10u/35V; C_1206_3216Metric; LCSC C13585
C27: 10n/600V; C_1206_3216Metric; LCSC C107201
J2: SS-60300-079; SS60300079; LCSC C402283
OP1: TLP283; SOP-4_4.4x2.6mm_P1.27mm; LCSC C55144
R36: 75R; R_1206_3216Metric; LCSC C17987
R47: 470R; R_0402_1005Metric; LCSC C25117
R48: 2K2; R_0402_1005Metric; LCSC C25879
TR1: WURTH_TR; WURTH1000T; LCSC C6828534
ZD3: BZT52C15S; SOD2513X120N; LCSC C19077448

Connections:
+24V_POE_IN: B1.+, B2.+, C22.1; also elsewhere on the board
/Jalapeno_8/MX1+: J2.7, TR1.23 (MX1+)
/Jalapeno_8/MX1-: J2.8, TR1.22 (MX1-)
/Jalapeno_8/MX2+: J2.5, TR1.20 (MX2+)
/Jalapeno_8/MX2-: J2.4, TR1.19 (MX2-)
/Jalapeno_8/MX3+: J2.6, TR1.17 (MX3+)
/Jalapeno_8/MX3-: J2.3, TR1.16 (MX3-)
/Jalapeno_8/MX4+: J2.2, TR1.14 (MX4+)
/Jalapeno_8/MX4-: J2.1, TR1.13 (MX4-)
GND: B1.-, B2.-, C21.1, C22.2, C23.1, C24.1, C25.1, C27.2, OP1.3 (EMIT); also elsewhere on the board
unnamed: C27.1, R36.1
unnamed: J2.MH1, J2.MH2, R36.2
unnamed: OP1.1 (A), R47.2, R48.2
unnamed: B1.AC2, OP1.2 (C), R47.1, TR1.15 (MCT4), ZD3.A, ZD3.C
unnamed: B2.AC1, TR1.24 (MCT1)
unnamed: B2.AC2, TR1.21 (MCT2)
unnamed: B1.AC1, R48.1, TR1.18 (MCT3)
unnamed: C21.2, TR1.1 (TCT1)
unnamed: C23.2, TR1.4 (TCT2)
unnamed: C24.2, TR1.7 (TCT3)
unnamed: C25.2, TR1.10 (TCT4)
P0TRX0+: TR1.11 (TD4+); also elsewhere on the board
P0TRX0-: TR1.12 (TD4-); also elsewhere on the board
P0TRX1+: TR1.8 (TD3+); also elsewhere on the board
P0TRX1-: TR1.9 (TD3-); also elsewhere on the board
P0TRX2+: TR1.5 (TD2+); also elsewhere on the board
P0TRX2-: TR1.6 (TD2-); also elsewhere on the board
P0TRX3+: TR1.2 (TD1+); also elsewhere on the board
P0TRX3-: TR1.3 (TD1-); also elsewhere on the board
RESET: OP1.4 (COL); also elsewhere on the board

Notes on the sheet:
Possible Eagle >> KiCad error

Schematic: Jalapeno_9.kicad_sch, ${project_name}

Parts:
B3, B4: 1A/50V; MBS; LCSC C2488
C26, C29, C30, C31: 100n/35V; C_0402_1005Metric; LCSC C187828
C28: 10n/600V; C_1206_3216Metric; LCSC C107201
C34: 10u/35V; C_1206_3216Metric; LCSC C13585
F1: 2A; Fuse_1812_4532Metric; LCSC C70124
J1: SS-60300-079; SS60300079; LCSC C402283
R37: 75R; R_1206_3216Metric; LCSC C17987
TR2: WURTH_TR; WURTH1000T; LCSC C6828534

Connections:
+24V_POE_OUT: F1.1; also elsewhere on the board
-24V_POE_O: B3.AC2, B4.AC2, C34.2; also elsewhere on the board
GND: C26.1, C28.2, C29.1, C30.1, C31.1; also elsewhere on the board
unnamed: B3.AC1, B4.AC1, C34.1, F1.2
unnamed: C28.1, R37.1
unnamed: J1.MH1, J1.MH2, R37.2
unnamed: B4.-, TR2.24 (MCT1)
unnamed: B4.+, TR2.21 (MCT2)
unnamed: B3.-, TR2.18 (MCT3)
unnamed: B3.+, TR2.15 (MCT4)
unnamed: J1.7, TR2.23 (MX1+)
unnamed: J1.8, TR2.22 (MX1-)
unnamed: J1.5, TR2.20 (MX2+)
unnamed: J1.4, TR2.19 (MX2-)
unnamed: J1.6, TR2.17 (MX3+)
unnamed: J1.3, TR2.16 (MX3-)
unnamed: J1.2, TR2.14 (MX4+)
unnamed: J1.1, TR2.13 (MX4-)
unnamed: C26.2, TR2.1 (TCT1)
unnamed: C29.2, TR2.4 (TCT2)
unnamed: C30.2, TR2.7 (TCT3)
unnamed: C31.2, TR2.10 (TCT4)
P1TRX0+: TR2.11 (TD4+); also elsewhere on the board
P1TRX0-: TR2.12 (TD4-); also elsewhere on the board
P1TRX1+: TR2.8 (TD3+); also elsewhere on the board
P1TRX1-: TR2.9 (TD3-); also elsewhere on the board
P1TRX2+: TR2.5 (TD2+); also elsewhere on the board
P1TRX2-: TR2.6 (TD2-); also elsewhere on the board
P1TRX3+: TR2.2 (TD1+); also elsewhere on the board
P1TRX3-: TR2.3 (TD1-); also elsewhere on the board

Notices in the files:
parts and their libraries:
project_license: CERN-OHL-S v2
